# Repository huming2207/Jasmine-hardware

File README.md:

# Project Jasmine
## Eagle schematic & PCB

### Project description

Project Jasmine is a smart LED light bulb, with built-in ESP8266 (ESP12F) WiFi SoC. 

### Author

Ming Hu (me)

Maohong Jiang (who designed the lamp base)

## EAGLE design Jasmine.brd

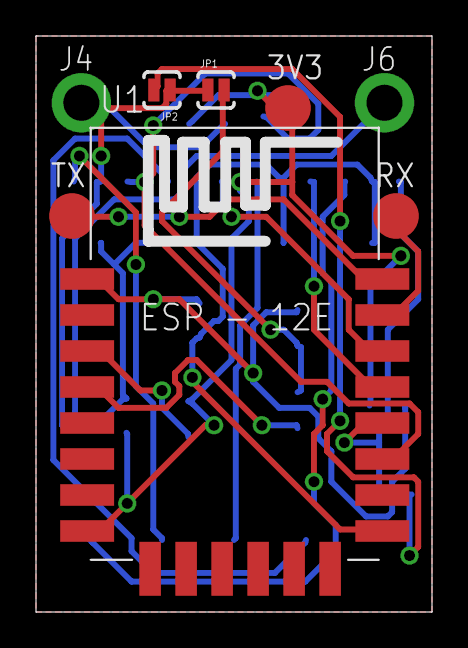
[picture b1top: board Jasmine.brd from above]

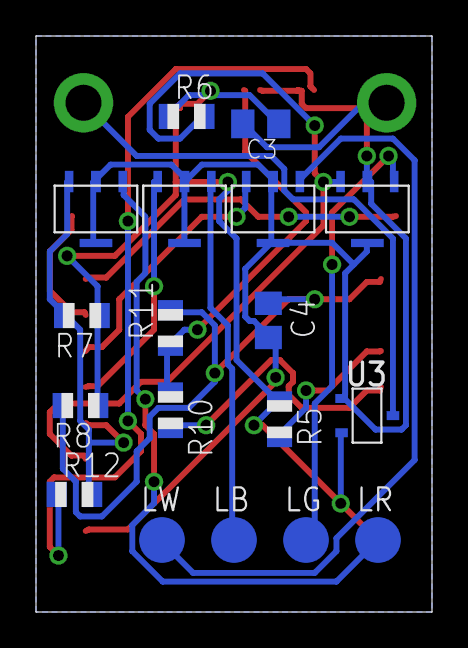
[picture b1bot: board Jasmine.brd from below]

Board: 2 copper layers, 22.0 x 32.0 mm, 26 parts (18 on the bottom side), 18 nets.

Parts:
3V3: TPB2,54; B2,54
C3: 1.0uF; C0805K
C4: 10uF; C0805
J4: GND; 1X01_2MM
J6: Vcc; 1X01_2MM
JP1: RST; SJ_2S-NO
JP2: BOOT; SJ_2S-NO
LB: TPB2,54; B2,54
LG: TPB2,54; B2,54
LR: TPB2,54; B2,54
LW: TPB2,54; B2,54
R5, R6, R7, R8: 12K; R0805
R10: 0R; R0805
R11, R12: 470R; R0805
RX: TPB2,54; B2,54
TX: TPB2,54; B2,54
U1: ESP-12F; ESP12E-SMD
U3: XC6206; XC6206_SOT-23
U$1, U$2, U$3, U$4: AMC7135_CC_REGULATOR

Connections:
+3V3: 3V3.TP, C3.1, R5.1, R6.1, R7.1, R8.1, U1.VCC, U3.2
CH_PD: R5.2, U1.CH_PD
GND: C3.2, C4.2, J4.1, JP1.1, JP2.1, U1.GND, U3.1, U$1.GND2, U$1.GND3, U$2.GND2, U$2.GND3, U$3.GND2, U$3.GND3, U$4.GND2, U$4.GND3
GPIO0: R7.2, R12.2, U1.GPIO0, U$2.VDD
GPIO2: R6.2, U1.GPIO2, U$1.VDD
GPIO4: U1.GPIO4, U$3.VDD
GPIO5: U1.GPIO5, U$4.VDD
JMP_BLDR: JP2.2, R12.1
JMP_RESET: JP1.2, R10.1, R11.1
LED_B: LB.TP, U$3.OUT
LED_G: LG.TP, U$1.OUT
LED_R: LR.TP, U$2.OUT
LED_W: LW.TP, U$4.OUT
RESET: C4.1, R8.2, R11.2, U1.RESET
RESET_WAKE: R10.2, U1.GPIO16
UART_RX: RX.TP, U1.RXD0
UART_TX: TX.TP, U1.TXD0
V+: J6.1, U3.3

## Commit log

2016-12-09 Initial commit for README
2016-12-09 Add a software (factory) reset jumper

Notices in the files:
parts and their libraries:
SparkFun-Connectors: Licensing: Creative Commons ShareAlike 4.0 International - https://creativecommons.org/licenses/by-sa/4.0
